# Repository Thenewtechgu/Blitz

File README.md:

# Blitz
Blitz is a MIMXRT1062DVJ6B based flight controller with dual Rp2350B for navigation and telemetry

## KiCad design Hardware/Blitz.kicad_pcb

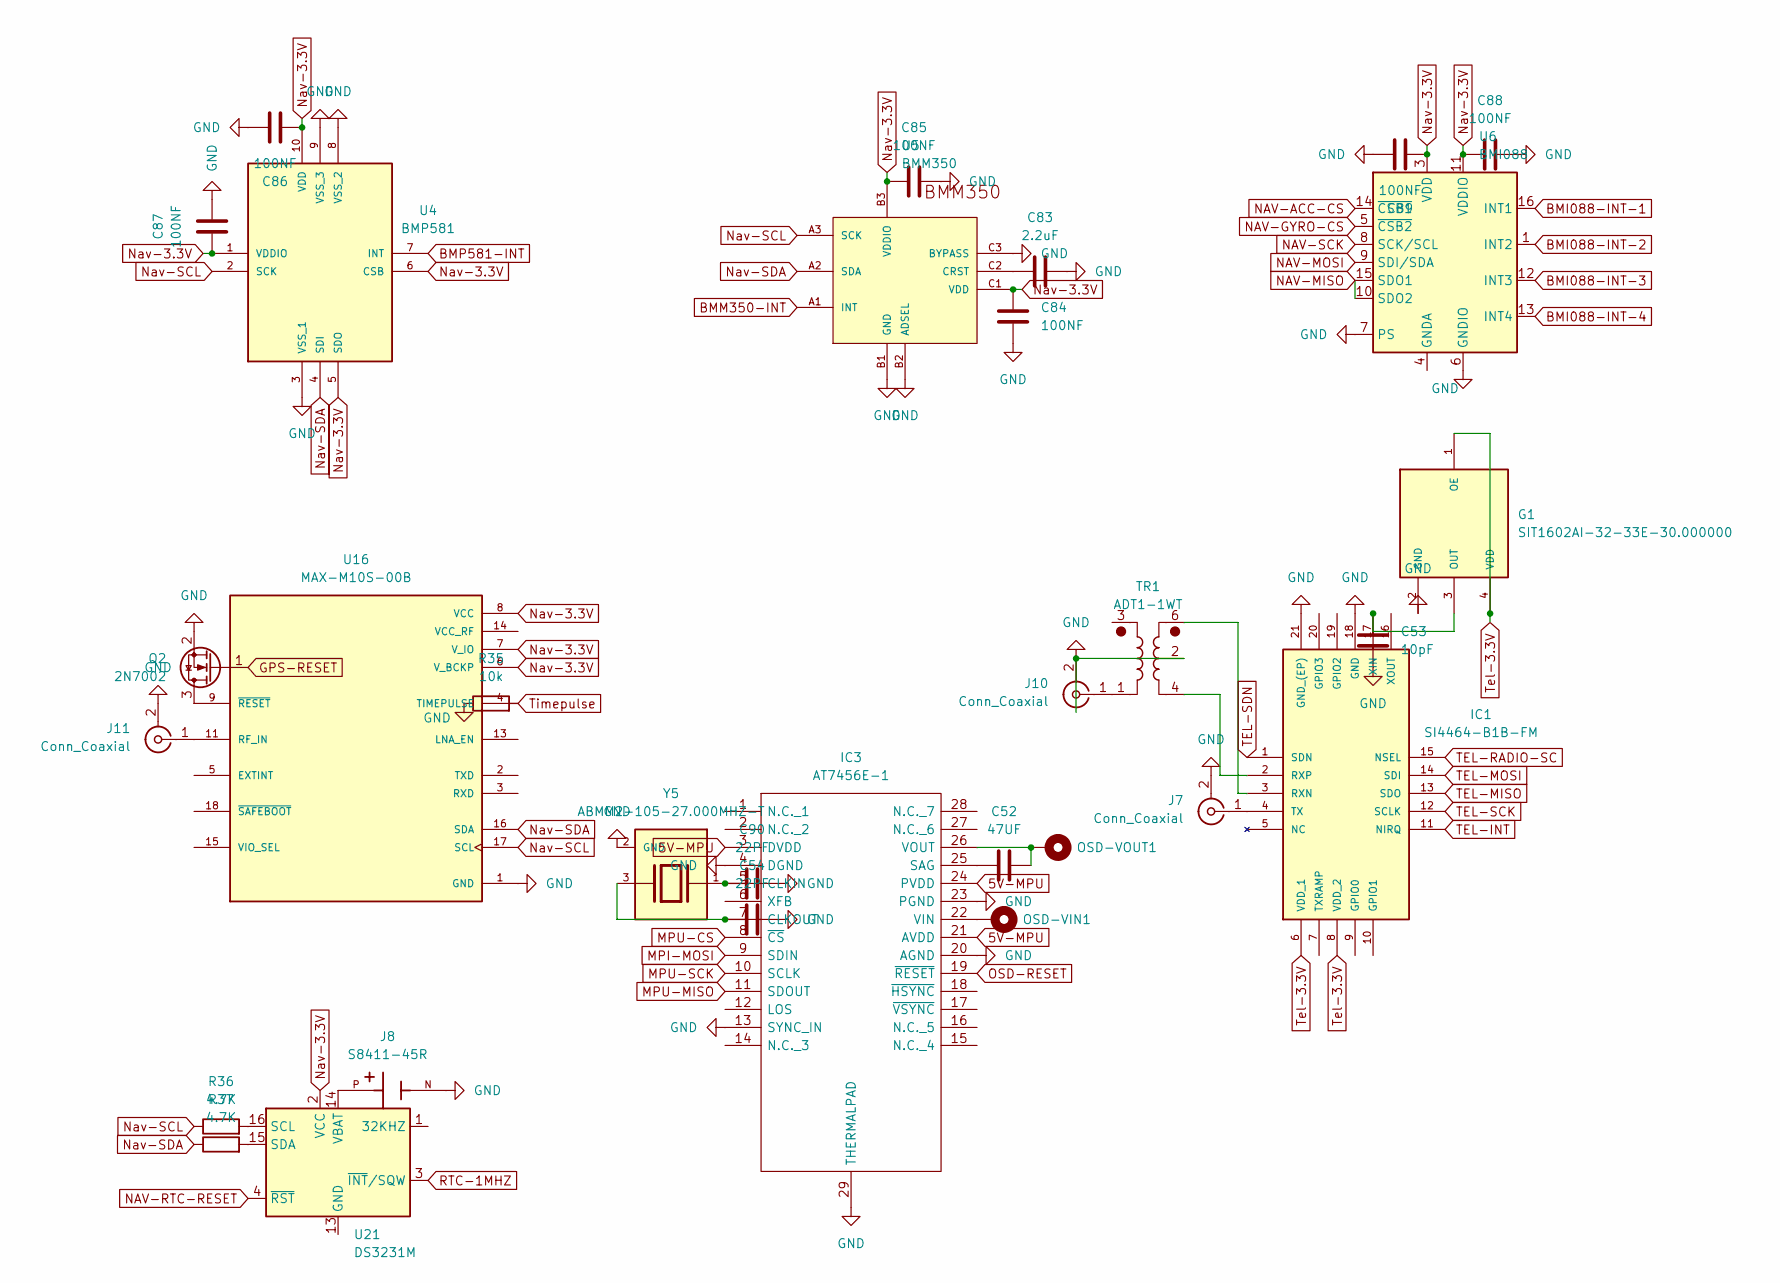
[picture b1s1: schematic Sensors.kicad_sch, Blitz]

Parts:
C52: 47UF; C_0402_1005Metric
C53: 10pF; C_0201_0603Metric
C54, C90: 22PF
C83: 2.2uF; C_0201_0603Metric
C84, C85, C86, C87, C88, C89: 100NF; C_0201_0603Metric
G1: SIT1602AI-32-33E-30.000000; OSC_SIT1602AI-32-33E-30.000000; PARTREV 1.2
IC1: SI4464-B1B-FM; QFN50P400X400X90-21N; MOUSER_PART_NUMBER 634-SI4464-B1X-FM
IC3: AT7456E-1; SOP65P640X120-29N; Manufacturer_Part_Number AT7456E
J7, J10, J11: Conn_Coaxial; SMA_Amphenol_901-143_Horizontal
J8: S8411-45R; HARWIN_S8411-45R; PARTREV 4
OSD-VIN1: Solderpad; TestPoint_Pad_1.5x1.5mm
OSD-VOUT1: Solderpad; TestPoint_Pad_1.5x1.5mm
Q2: 2N7002; SOT-23
R35: 10k; R_0201_0603Metric
R36, R37: 4.7K; R_0201_0603Metric
TR1: ADT1-1WT; Mini-Circuits_CD542_H2.84mm
U4: BMP581; Manufacturer_Part_Number BMP581
U5: BMM350; BGA9C40P3X3_128X128X50
U6: BMI088; Bosch_LGA-16_4.5x3mm_P0.5mm_LayoutBorder7x1y_ClockwisePinNu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
U16: MAX-M10S-00B; XCVR_MAX-M10S-00B; PARTREV C1
U21: DS3231M; SOIC-16W_7.5x10.3mm_P1.27mm
Y5: ABMM2-105-27.000MHZ-T; XTAL_ABMM2-105-27.000MHZ-T; PARTREV 01.18.13

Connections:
5V-MPU: IC3.3 (DVDD), IC3.21 (AVDD), IC3.24 (PVDD); also elsewhere on the board
BMI088-INT-1: U6.16 (INT1); also elsewhere on the board
BMI088-INT-2: U6.1 (INT2); also elsewhere on the board
BMI088-INT-3: U6.12 (INT3); also elsewhere on the board
BMI088-INT-4: U6.13 (INT4); also elsewhere on the board
BMM350-INT: U5.A1 (INT); also elsewhere on the board
BMP581-INT: U4.7 (INT); also elsewhere on the board
GPS-RESET: Q2.1 (G); also elsewhere on the board
MPI-MOSI: IC3.9 (SDIN); also elsewhere on the board
MPU-CS: IC3.8 (~CS); also elsewhere on the board
MPU-MISO: IC3.11 (SDOUT); also elsewhere on the board
MPU-SCK: IC3.10 (SCLK); also elsewhere on the board
NAV-ACC-CS: U6.14 (~CSB1); also elsewhere on the board
NAV-GYRO-CS: U6.5 (~CSB2); also elsewhere on the board
NAV-MISO: U6.10 (SDO2), U6.15 (SDO1); also elsewhere on the board
NAV-MOSI: U6.9 (SDI/SDA); also elsewhere on the board
NAV-RTC-RESET: U21.4 (~RST)
NAV-SCK: U6.8 (SCK/SCL); also elsewhere on the board
Nav-3.3V: C84.1, C85.1, C86.1, C87.1, C88.1, C89.1, U4.1 (VDDIO), U4.5 (SDO), U4.6 (CSB), U4.10 (VDD), U5.B3 (VDDIO), U5.C1 (VDD), U6.3 (VDD), U6.11 (VDDIO), U16.6 (V_BCKP), U16.7 (V_IO), U16.8 (VCC), U21.2 (VCC); also elsewhere on the board
Nav-SCL: R36.1, U4.2 (SCK), U5.A3 (SCK), U16.17 (SCL)
Nav-SDA: R37.1, U4.4 (SDI), U5.A2 (SDA), U16.16 (SDA)
unnamed: C53.1, G1.3 (OUT), IC1.17 (XIN)
unnamed: IC1.3 (RXN), TR1.6
unnamed: IC1.2 (RXP), TR1.4
unnamed: IC1.4 (TX), J7.1 (In)
unnamed: C90.1, IC3.5 (CLKIN), Y5.1
unnamed: C54.1, IC3.7 (CLKOUT), Y5.3
unnamed: C52.1, IC3.25 (SAG)
unnamed: IC3.22 (VIN), OSD-VIN1.1
unnamed: C52.2, IC3.26 (VOUT), OSD-VOUT1.1
unnamed: J10.1 (In), TR1.1
unnamed: J11.1 (In), U16.11 (RF_IN)
unnamed: Q2.3 (D), U16.9 (~RESET)
unnamed: C83.1, U5.C2 (CRST)
unnamed: U6.2 (GNDA), U6.4 (GNDA)
unnamed: U21.5 (GND), U21.6 (GND), U21.7 (GND), U21.8 (GND), U21.9 (GND), U21.10 (GND), U21.11 (GND), U21.12 (GND), U21.13 (GND)
unnamed: R36.2, U21.16 (SCL)
unnamed: R37.2, U21.15 (SDA)
unnamed: J8.P, U21.14 (VBAT)
OSD-RESET: IC3.19 (~RESET); also elsewhere on the board
RTC-1MHZ: U21.3 (~INT/SQW); also elsewhere on the board
TEL-INT: IC1.11 (NIRQ); also elsewhere on the board
TEL-MISO: IC1.13 (SDO); also elsewhere on the board
TEL-MOSI: IC1.14 (SDI); also elsewhere on the board
TEL-RADIO-SC: IC1.15 (NSEL); also elsewhere on the board
TEL-SCK: IC1.12 (SCLK); also elsewhere on the board
TEL-SDN: IC1.1 (SDN); also elsewhere on the board
Tel-3.3V: G1.1 (OE), G1.4 (VDD), IC1.6 (VDD_1), IC1.8 (VDD_2); also elsewhere on the board
Timepulse: R35.2, U16.4 (TIMEPULSE); also elsewhere on the board

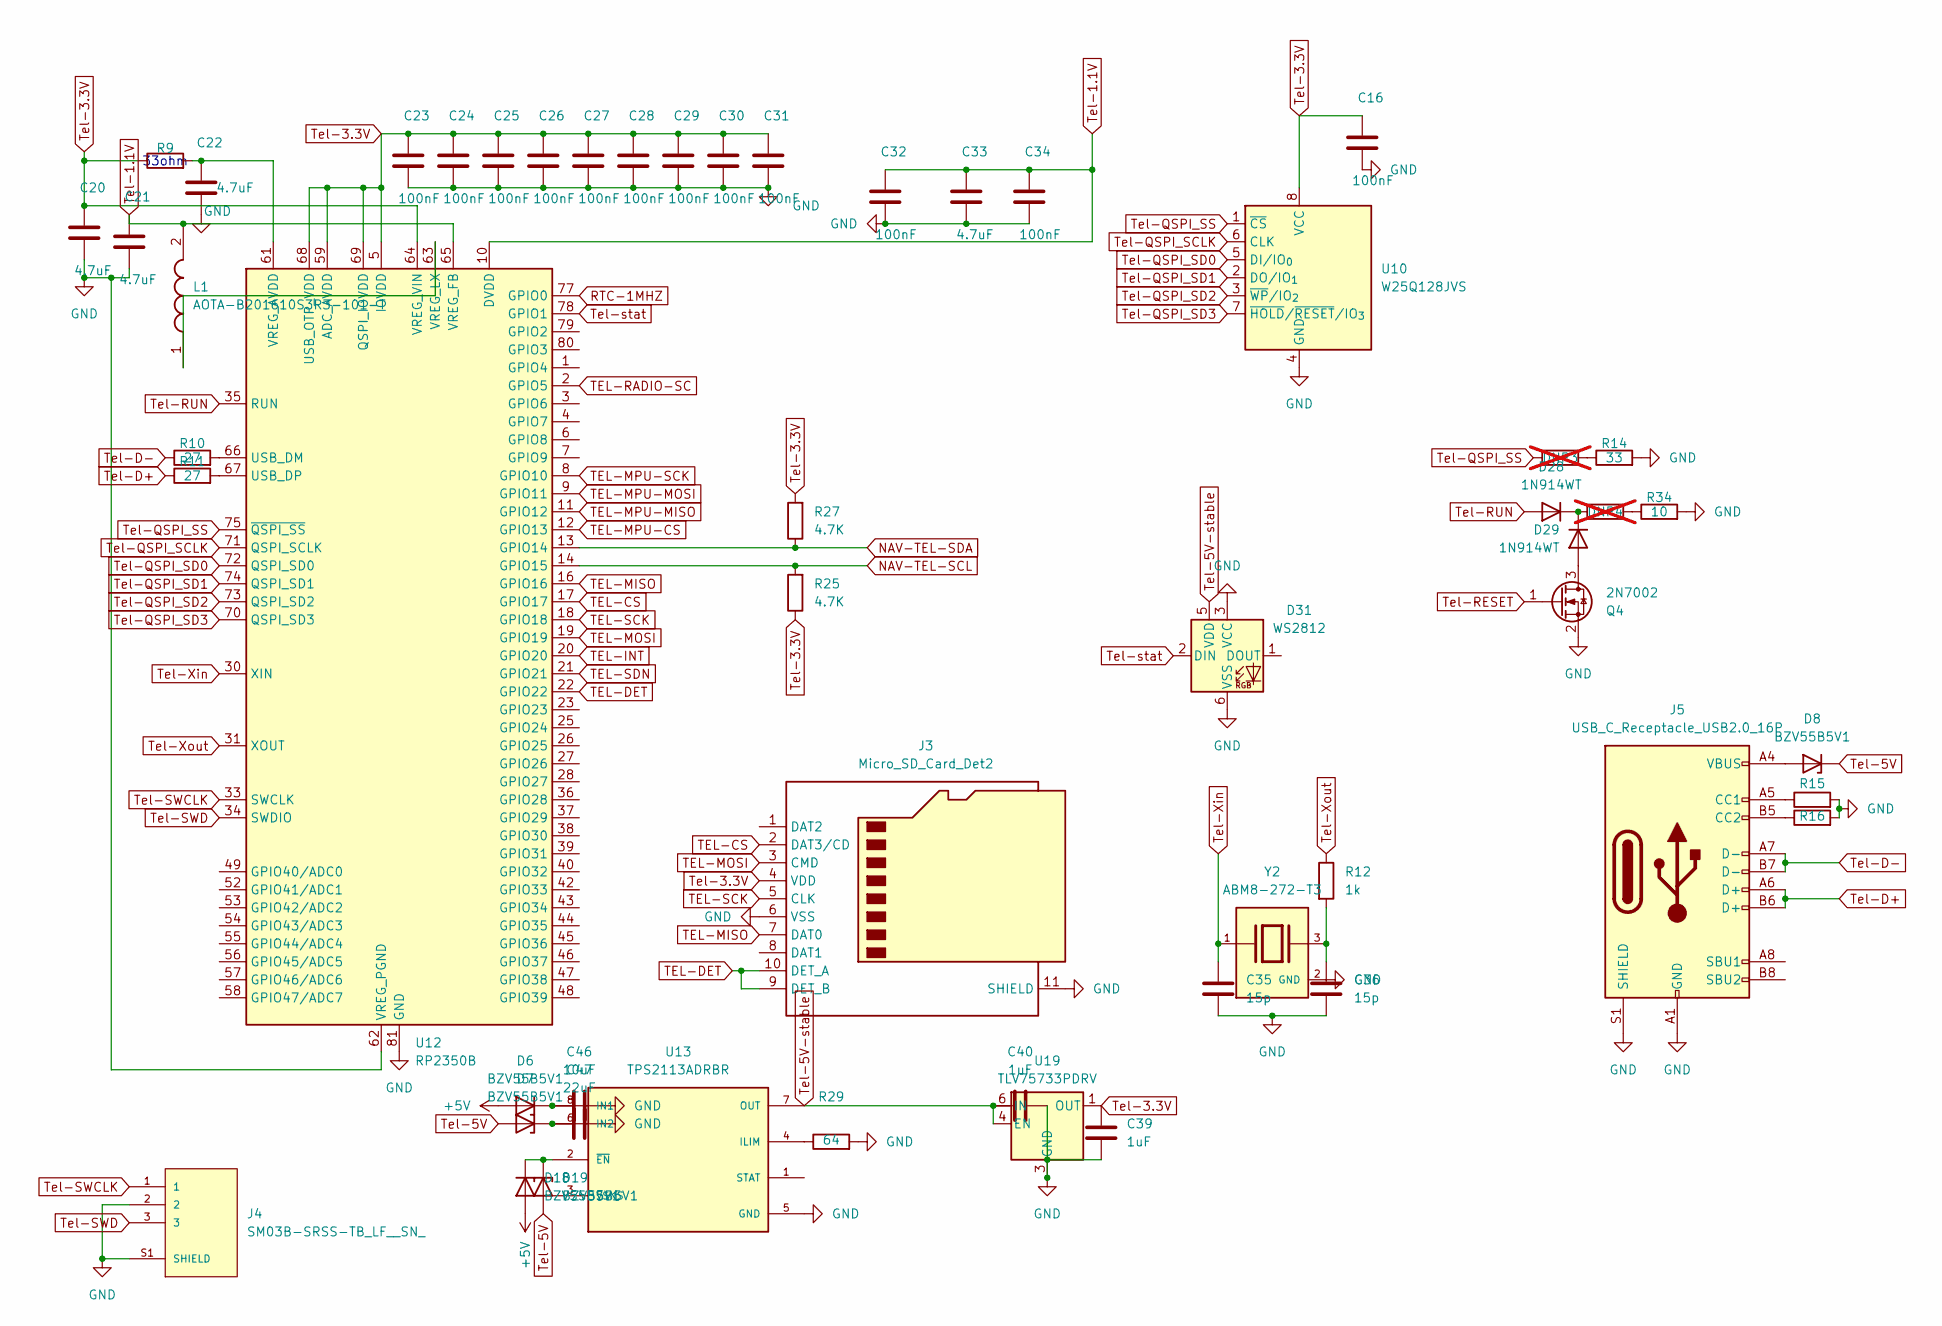
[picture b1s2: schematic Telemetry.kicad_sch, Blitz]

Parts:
C16, C23, C24, C25, C26, C27, C28, C29, C30, C31, C32, C34: 100nF; C_01005_0402Metric
C20, C21, C22, C33: 4.7uF; C_01005_0402Metric
C35, C36: 15p; C_0201_0603Metric
C39, C40: 1uF; C_0402_1005Metric
C46: 10uF; C_1206_3216Metric_Pad1.33x1.80mm_HandSolder
C47: 22uF; C_1206_3216Metric_Pad1.33x1.80mm_HandSolder
D6, D7, D8, D18, D19: BZV55B5V1; D_MiniMELF
D28, D29: 1N914WT; D_SOD-523
D31: WS2812; LED_WS2812_PLCC6_5.0x5.0mm_P1.6mm
DNP3, DNP4: R; R_2010_5025Metric_Pad1.40x2.65mm_HandSolder; not fitted
J3: Micro_SD_Card_Det2; microSD_HC_Molex_104031-0811
J4: SM03B-SRSS-TB_LF__SN_; JST_SM03B-SRSS-TB_LF__SN_
J5: USB_C_Receptacle_USB2.0_16P; USB_C_Receptacle_G-Switch_GT-USB-7010ASV
L1: AOTA-B201610S3R3-101-T; AOTAB201610S3R3101T; Manufacturer_Part_Number AOTA-B201610S3R3-101-T; Mouser Part Number 815-AB201610S3R3101T
Q4: 2N7002; SOT-23
R9: R; R_01005_0402Metric_Pad0.57x0.30mm_HandSolder
R10, R11: 27; R_0201_0603Metric_Pad0.64x0.40mm_HandSolder
R12: 1k; R_01005_0402Metric
R14: 33; R_0201_0603Metric_Pad0.64x0.40mm_HandSolder
R15, R16: R; R_01005_0402Metric
R25, R27: 4.7K; R_0201_0603Metric
R29: 64; R_0201_0603Metric
R34: 10; R_0201_0603Metric_Pad0.64x0.40mm_HandSolder
U10: W25Q128JVS; SOIC-8_5.3x5.3mm_P1.27mm
U12: RP2350B; QFN-80-1EP_10x10mm_P0.4mm_EP3.4x3.4mm
U13: TPS2113ADRBR; SON65P300X300X100-9N; PARTREV C
U19: TLV75733PDRV; WSON-6-1EP_2x2mm_P0.65mm_EP1x1.6mm
Y2: ABM8-272-T3; XTAL_ABM8-272-T3; PARTREV 07-29-20

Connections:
+5V: D6.2 (A), D18.2 (A); also elsewhere on the board
NAV-TEL-SCL: R25.2, U12.14 (GPIO15); also elsewhere on the board
NAV-TEL-SDA: R27.1, U12.13 (GPIO14); also elsewhere on the board
unnamed: C36.1, R12.2, Y2.3
unnamed: C46.1, D6.1 (K), U13.8 (IN1)
unnamed: C47.1, D7.1 (K), U13.6 (IN2)
unnamed: D8.2 (A), J5.A4 (VBUS), J5.A9 (VBUS), J5.B4 (VBUS), J5.B9 (VBUS)
unnamed: D18.1 (K), D19.1 (K), U13.2 (~EN)
unnamed: D28.1 (K), D29.1 (K), DNP4.1
unnamed: D29.2 (A), Q4.3 (D)
unnamed: DNP3.2, R14.1
unnamed: DNP4.2, R34.1
unnamed: J5.A5 (CC1), R15.1
unnamed: J5.B5 (CC2), R16.1
unnamed: R10.2, U12.66 (USB_DM)
unnamed: R11.2, U12.67 (USB_DP)
unnamed: C22.1, R9.2, U12.61 (VREG_AVDD)
unnamed: L1.1, U12.63 (VREG_LX)
unnamed: R29.1, U13.4 (ILIM)
RTC-1MHZ: U12.77 (GPIO0); also elsewhere on the board
TEL-CS: J3.2 (DAT3/CD), U12.17 (GPIO17)
TEL-DET: J3.9 (DET_B), J3.10 (DET_A), U12.22 (GPIO22)
TEL-INT: U12.20 (GPIO20); also elsewhere on the board
TEL-MISO: J3.7 (DAT0), U12.16 (GPIO16); also elsewhere on the board
TEL-MOSI: J3.3 (CMD), U12.19 (GPIO19); also elsewhere on the board
TEL-MPU-CS: U12.12 (GPIO13); also elsewhere on the board
TEL-MPU-MISO: U12.11 (GPIO12); also elsewhere on the board
TEL-MPU-MOSI: U12.9 (GPIO11); also elsewhere on the board
TEL-MPU-SCK: U12.8 (GPIO10); also elsewhere on the board
TEL-RADIO-SC: U12.2 (GPIO5); also elsewhere on the board
TEL-SCK: J3.5 (CLK), U12.18 (GPIO18); also elsewhere on the board
TEL-SDN: U12.21 (GPIO21); also elsewhere on the board
Tel-1.1V: C21.1, C32.1, C33.1, C34.1, L1.2, U12.10 (DVDD), U12.32 (DVDD), U12.51 (DVDD), U12.65 (VREG_FB)
Tel-3.3V: C16.1, C20.1, C23.1, C24.1, C25.1, C26.1, C27.1, C28.1, C29.1, C30.1, C31.1, C39.1, J3.4 (VDD), R9.1, R25.1, R27.2, U10.8 (VCC), U12.5 (IOVDD), U12.15 (IOVDD), U12.24 (IOVDD), U12.29 (IOVDD), U12.41 (IOVDD), U12.50 (IOVDD), U12.59 (ADC_AVDD), U12.60 (IOVDD), U12.64 (VREG_VIN), U12.68 (USB_OTP_VDD), U12.69 (QSPI_IOVDD), U12.76 (IOVDD), U19.1 (OUT); also elsewhere on the board
Tel-5V: D7.2 (A), D8.1 (K), D19.2 (A)
Tel-5V-stable: C40.1, D31.5 (VDD), U13.7 (OUT), U19.4 (EN), U19.6 (IN)
Tel-D+: J5.A6 (D+), J5.B6 (D+), R11.1
Tel-D-: J5.A7 (D-), J5.B7 (D-), R10.1
Tel-QSPI_SCLK: U10.6 (CLK), U12.71 (QSPI_SCLK)
Tel-QSPI_SD0: U10.5 (DI/IO_{0}), U12.72 (QSPI_SD0)
Tel-QSPI_SD1: U10.2 (DO/IO_{1}), U12.74 (QSPI_SD1)
Tel-QSPI_SD2: U10.3 (~WP/IO_{2}), U12.73 (QSPI_SD2)
Tel-QSPI_SD3: U10.7 (~HOLD/~RESET/IO_{3}), U12.70 (QSPI_SD3)
Tel-QSPI_SS: DNP3.1, U10.1 (~CS), U12.75 (~QSPI_SS)
Tel-RESET: Q4.1 (G)
Tel-RUN: D28.2 (A), U12.35 (RUN)
Tel-SWCLK: J4.1, U12.33 (SWCLK)
Tel-SWD: J4.3, U12.34 (SWDIO)
Tel-Xin: C35.1, U12.30 (XIN), Y2.1
Tel-Xout: R12.1, U12.31 (XOUT)
Tel-stat: D31.2 (DIN), U12.78 (GPIO1)

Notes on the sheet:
33ohm

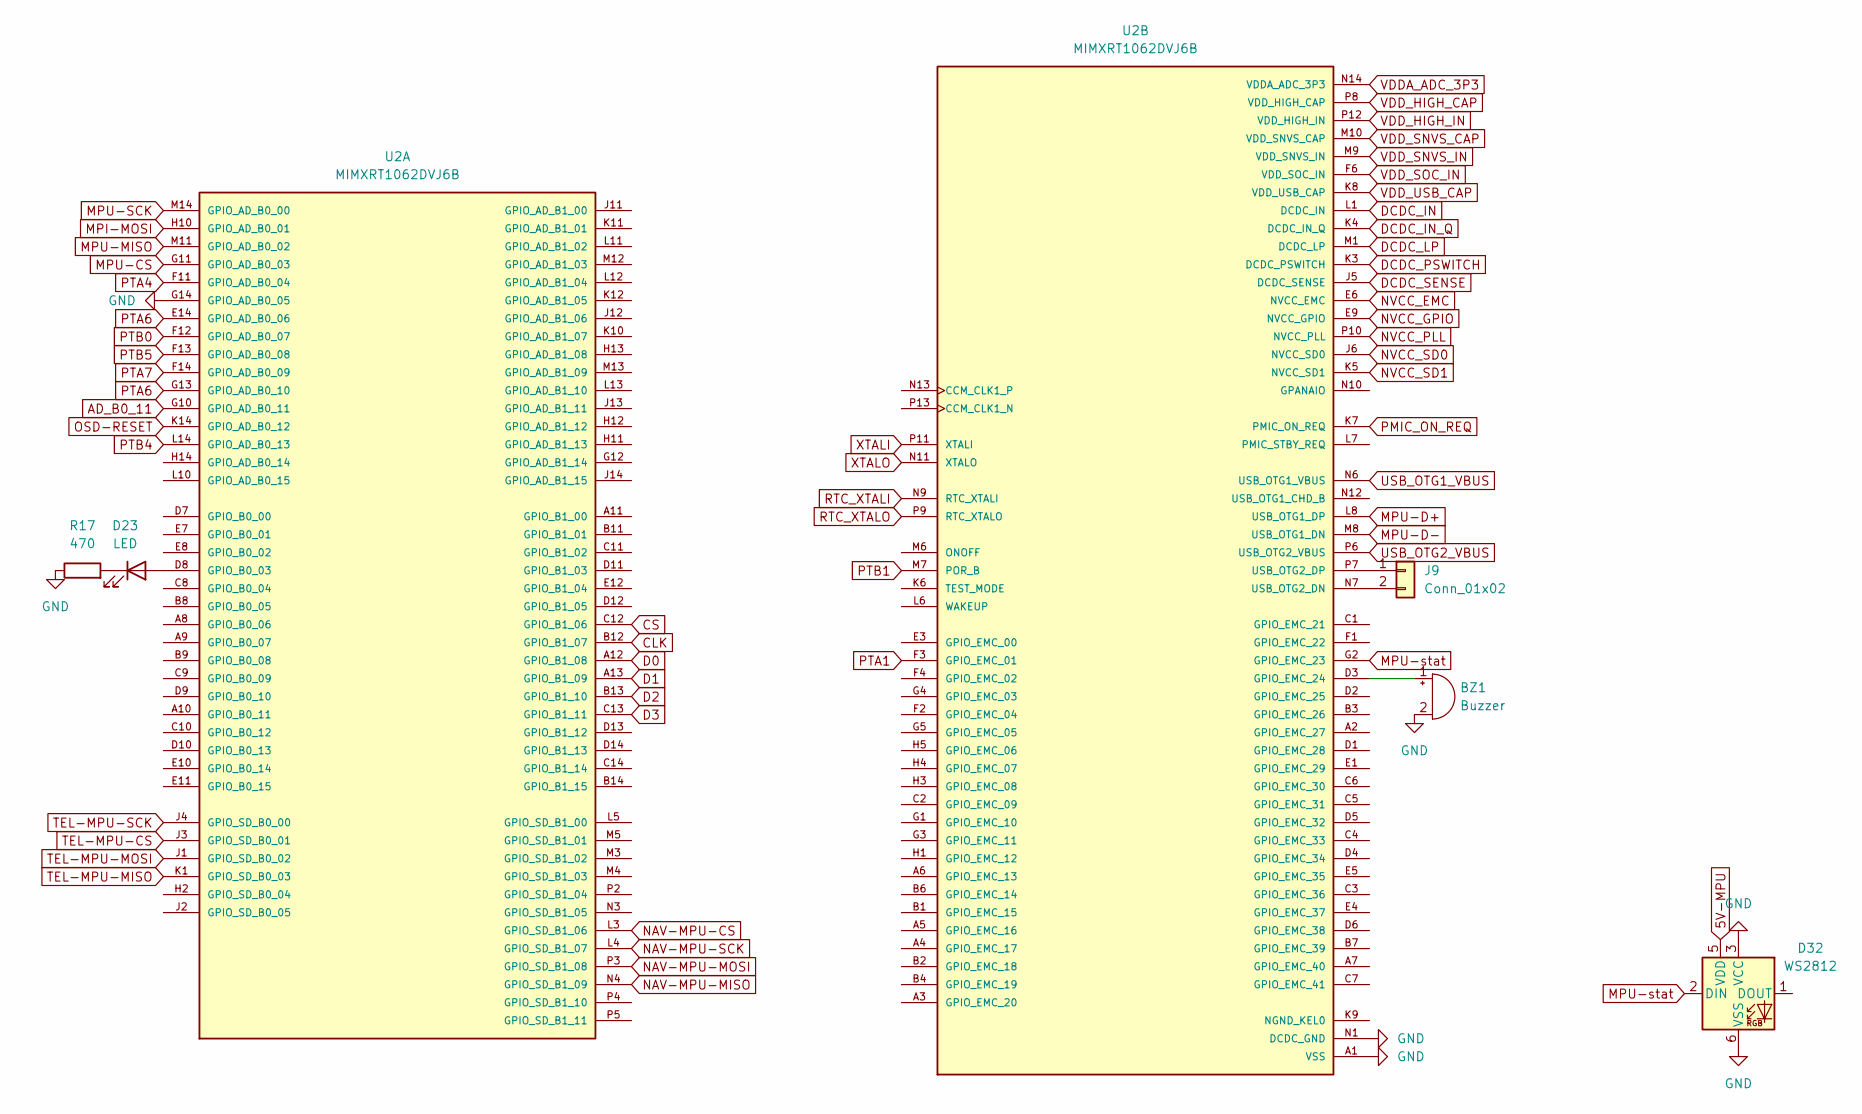
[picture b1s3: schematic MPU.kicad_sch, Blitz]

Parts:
BZ1: Buzzer; MLT-8530_JHE_1
D23: LED; LED_1206_3216Metric_Pad1.42x1.75mm_HandSolder
D32: WS2812; LED_WS2812_PLCC6_5.0x5.0mm_P1.6mm
J9: Conn_01x02; PinSocket_1x02_P1.00mm_Vertical
R17: 470; R_0201_0603Metric_Pad0.64x0.40mm_HandSolder
U2: MIMXRT1062DVJ6B; BGA196C80P14X14_1200X1200X152N; PARTREV 3

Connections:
5V-MPU: D32.5 (VDD); also elsewhere on the board
AD_B0_11: U2.G10 (GPIO_AD_B0_11), U2.K3 (DCDC_PSWITCH); also elsewhere on the board
CLK: U2.B12 (GPIO_B1_07); also elsewhere on the board
CS: U2.C12 (GPIO_B1_06); also elsewhere on the board
D0: U2.A12 (GPIO_B1_08); also elsewhere on the board
D1: U2.A13 (GPIO_B1_09); also elsewhere on the board
D2: U2.B13 (GPIO_B1_10); also elsewhere on the board
D3: U2.C13 (GPIO_B1_11); also elsewhere on the board
DCDC_IN: U2.L1 (DCDC_IN), U2.L2 (DCDC_IN); also elsewhere on the board
DCDC_IN_Q: U2.E6 (NVCC_EMC), U2.E9 (NVCC_GPIO), U2.F5 (NVCC_EMC), U2.F6 (VDD_SOC_IN), U2.F7 (VDD_SOC_IN), U2.F8 (VDD_SOC_IN), U2.F9 (VDD_SOC_IN), U2.F10 (NVCC_GPIO), U2.G6 (VDD_SOC_IN), U2.G9 (VDD_SOC_IN), U2.H6 (VDD_SOC_IN), U2.H9 (VDD_SOC_IN), U2.J5 (DCDC_SENSE), U2.J6 (NVCC_SD0), U2.J9 (VDD_SOC_IN), U2.J10 (NVCC_GPIO), U2.K4 (DCDC_IN_Q), U2.K5 (NVCC_SD1), U2.N14 (VDDA_ADC_3P3), U2.P12 (VDD_HIGH_IN); also elsewhere on the board
DCDC_LP: U2.M1 (DCDC_LP), U2.M2 (DCDC_LP); also elsewhere on the board
MPI-MOSI: U2.H10 (GPIO_AD_B0_01); also elsewhere on the board
MPU-CS: U2.G11 (GPIO_AD_B0_03); also elsewhere on the board
MPU-D+: U2.L8 (USB_OTG1_DP); also elsewhere on the board
MPU-D-: U2.M8 (USB_OTG1_DN); also elsewhere on the board
MPU-MISO: U2.M11 (GPIO_AD_B0_02); also elsewhere on the board
MPU-SCK: U2.M14 (GPIO_AD_B0_00); also elsewhere on the board
MPU-stat: D32.2 (DIN), U2.G2 (GPIO_EMC_23)
NAV-MPU-CS: U2.L3 (GPIO_SD_B1_06); also elsewhere on the board
NAV-MPU-MISO: U2.N4 (GPIO_SD_B1_09); also elsewhere on the board
NAV-MPU-MOSI: U2.P3 (GPIO_SD_B1_08); also elsewhere on the board
NAV-MPU-SCK: U2.L4 (GPIO_SD_B1_07); also elsewhere on the board
NVCC_PLL: U2.P10 (NVCC_PLL); also elsewhere on the board
unnamed: BZ1.1 (+), U2.D3 (GPIO_EMC_24)
unnamed: D23.2 (A), U2.D8 (GPIO_B0_03)
unnamed: D23.1 (K), R17.2
unnamed: J9.1, U2.P7 (USB_OTG2_DP)
unnamed: J9.2, U2.N7 (USB_OTG2_DN)
OSD-RESET: U2.K14 (GPIO_AD_B0_12); also elsewhere on the board
PMIC_ON_REQ: U2.K7 (PMIC_ON_REQ); also elsewhere on the board
PTA1: U2.F3 (GPIO_EMC_01); also elsewhere on the board
PTA4: U2.F11 (GPIO_AD_B0_04); also elsewhere on the board
PTA6: U2.E14 (GPIO_AD_B0_06), U2.G13 (GPIO_AD_B0_10); also elsewhere on the board
PTA7: U2.F14 (GPIO_AD_B0_09); also elsewhere on the board
PTB0: U2.F12 (GPIO_AD_B0_07); also elsewhere on the board
PTB1: U2.M7 (POR_B); also elsewhere on the board
PTB4: U2.L14 (GPIO_AD_B0_13); also elsewhere on the board
PTB5: U2.F13 (GPIO_AD_B0_08); also elsewhere on the board
RTC_XTALI: U2.N9 (RTC_XTALI); also elsewhere on the board
RTC_XTALO: U2.P9 (RTC_XTALO); also elsewhere on the board
TEL-MPU-CS: U2.J3 (GPIO_SD_B0_01); also elsewhere on the board
TEL-MPU-MISO: U2.K1 (GPIO_SD_B0_03); also elsewhere on the board
TEL-MPU-MOSI: U2.J1 (GPIO_SD_B0_02); also elsewhere on the board
TEL-MPU-SCK: U2.J4 (GPIO_SD_B0_00); also elsewhere on the board
USB_OTG1_VBUS: U2.N6 (USB_OTG1_VBUS), U2.P6 (USB_OTG2_VBUS); also elsewhere on the board
VDD_HIGH_CAP: U2.P8 (VDD_HIGH_CAP); also elsewhere on the board
VDD_SNVS_CAP: U2.M10 (VDD_SNVS_CAP); also elsewhere on the board
VDD_SNVS_IN: U2.M9 (VDD_SNVS_IN); also elsewhere on the board
VDD_USB_CAP: U2.K8 (VDD_USB_CAP); also elsewhere on the board
XTALI: U2.P11 (XTALI); also elsewhere on the board
XTALO: U2.N11 (XTALO); also elsewhere on the board

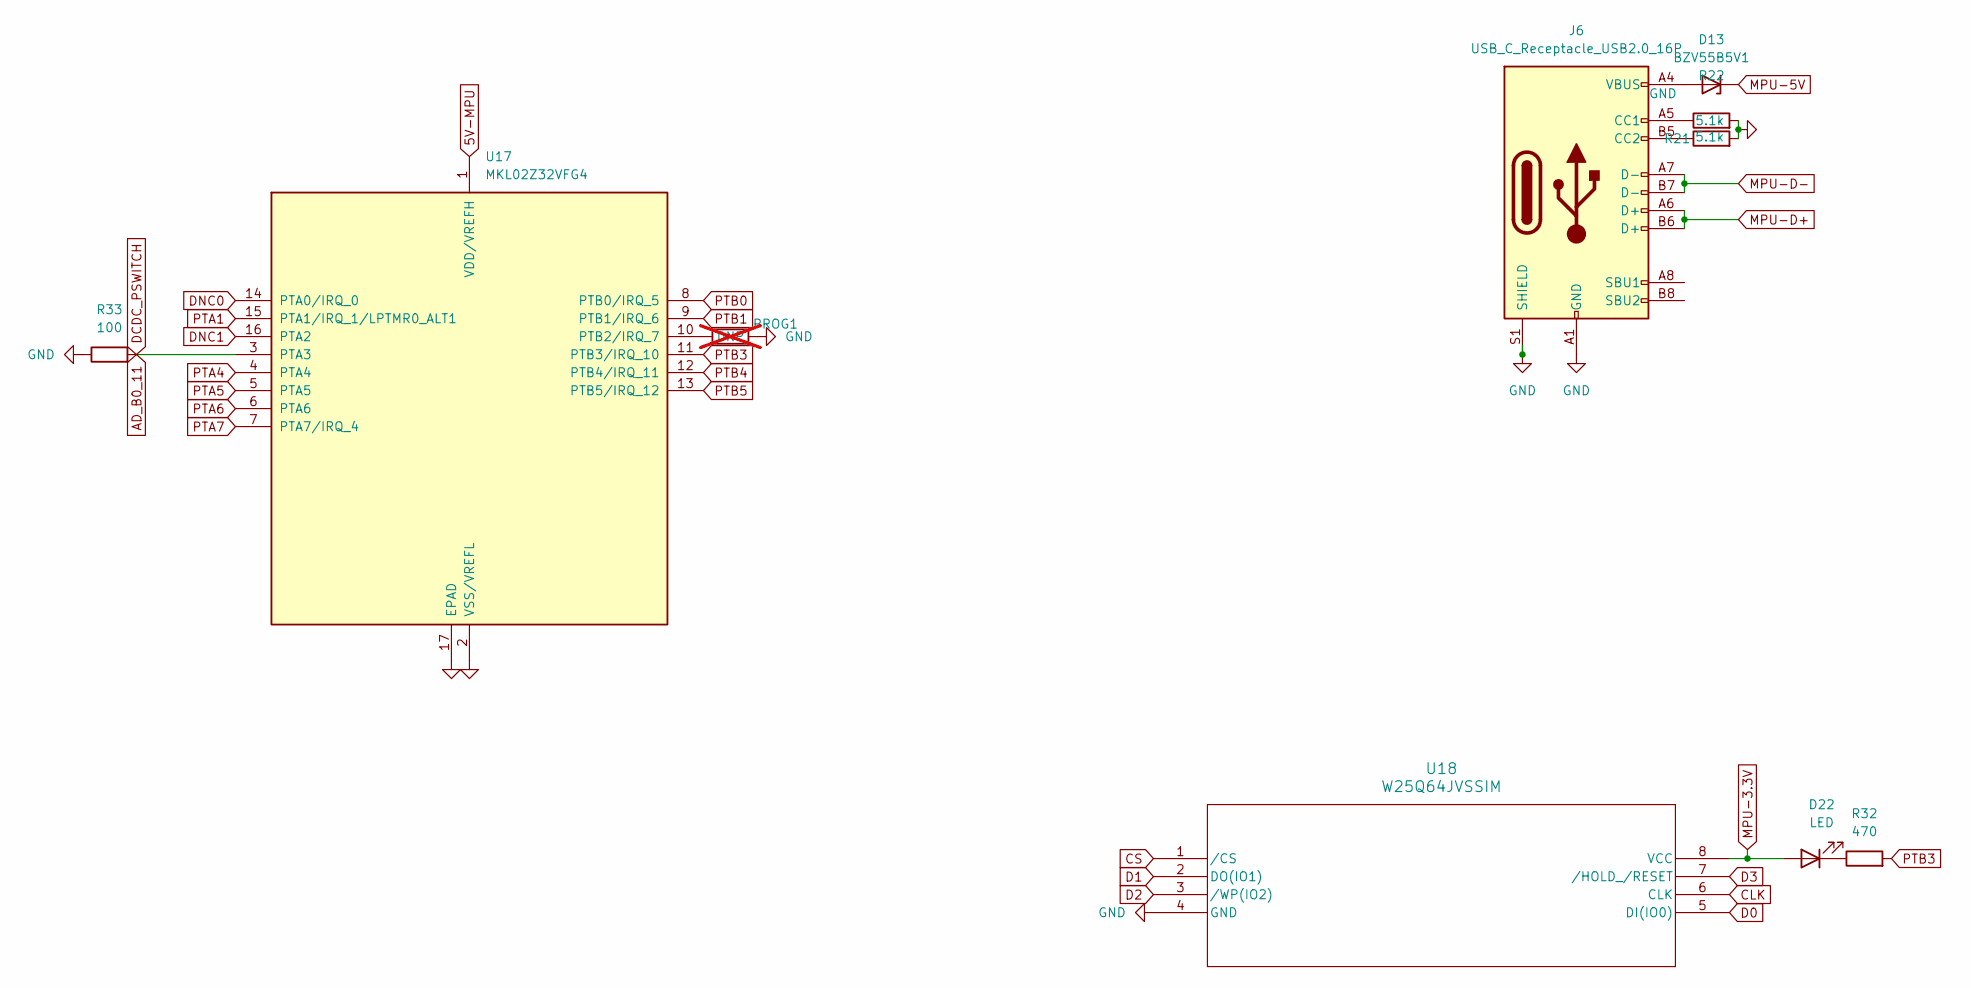
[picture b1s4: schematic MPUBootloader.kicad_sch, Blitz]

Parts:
D13: BZV55B5V1; D_MiniMELF
D22: LED; LED_1206_3216Metric
J6: USB_C_Receptacle_USB2.0_16P; USB_C_Receptacle_G-Switch_GT-USB-7010ASV
PROG1: DNP; R_2010_5025Metric_Pad1.40x2.65mm_HandSolder; not fitted
R21, R22: 5.1k; R_0201_0603Metric
R32: 470; R_0201_0603Metric
R33: 100; R_0201_0603Metric
U17: MKL02Z32VFG4; QFN-16-1EP_3x3mm_P0.5mm_EP1.9x1.9mm
U18: W25Q64JVSSIM; SOIC_208MIL_WIN

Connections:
5V-MPU: U17.1 (VDD/VREFH); also elsewhere on the board
AD_B0_11: R33.2, U17.3 (PTA3); also elsewhere on the board
CLK: U18.6 (CLK); also elsewhere on the board
CS: U18.1 (/CS); also elsewhere on the board
D0: U18.5 (DI(IO0)); also elsewhere on the board
D1: U18.2 (DO(IO1)); also elsewhere on the board
D2: U18.3 (/WP(IO2)); also elsewhere on the board
D3: U18.7 (/HOLD_/RESET); also elsewhere on the board
DCDC_IN_Q: D22.2 (A), U18.8 (VCC); also elsewhere on the board
DNC0: U17.14 (PTA0/IRQ_0)
DNC1: U17.16 (PTA2)
MPU-5V: D13.1 (K); also elsewhere on the board
MPU-D+: J6.A6 (D+), J6.B6 (D+); also elsewhere on the board
MPU-D-: J6.A7 (D-), J6.B7 (D-); also elsewhere on the board
unnamed: D13.2 (A), J6.A4 (VBUS), J6.A9 (VBUS), J6.B4 (VBUS), J6.B9 (VBUS)
unnamed: D22.1 (K), R32.1
unnamed: J6.A5 (CC1), R22.1
unnamed: J6.B5 (CC2), R21.1
unnamed: PROG1.1, U17.10 (PTB2/IRQ_7)
PTA1: U17.15 (PTA1/IRQ_1/LPTMR0_ALT1); also elsewhere on the board
PTA4: U17.4 (PTA4); also elsewhere on the board
PTA5: U17.5 (PTA5)
PTA6: U17.6 (PTA6); also elsewhere on the board
PTA7: U17.7 (PTA7/IRQ_4); also elsewhere on the board
PTB0: U17.8 (PTB0/IRQ_5); also elsewhere on the board
PTB1: U17.9 (PTB1/IRQ_6); also elsewhere on the board
PTB3: R32.2, U17.11 (PTB3/IRQ_10)
PTB4: U17.12 (PTB4/IRQ_11); also elsewhere on the board
PTB5: U17.13 (PTB5/IRQ_12); also elsewhere on the board

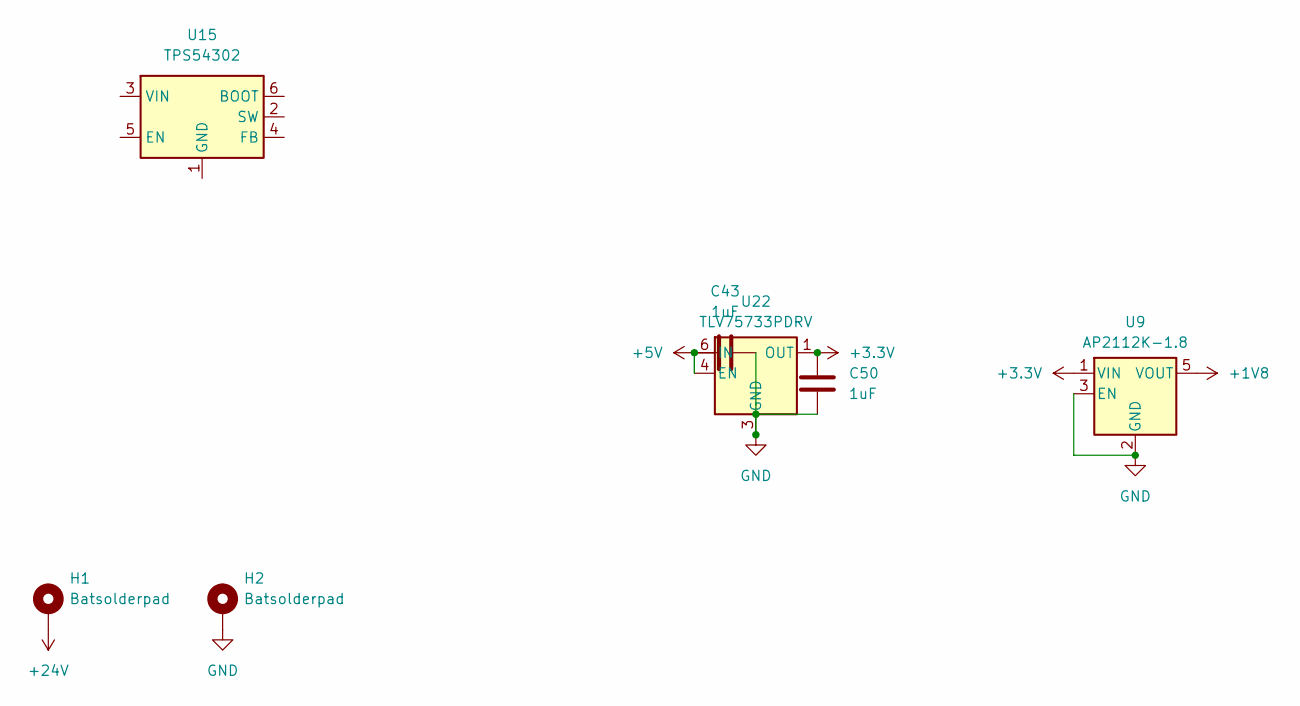
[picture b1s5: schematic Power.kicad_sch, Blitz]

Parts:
C43, C50: 1uF; C_1206_3216Metric_Pad1.33x1.80mm_HandSolder
H1, H2: Batsolderpad; TestPoint_Pad_4.0x4.0mm
U9: AP2112K-1.8; SOT-23-5
U15: TPS54302; SOT-23-6
U22: TLV75733PDRV; WSON-6-1EP_2x2mm_P0.65mm_EP1x1.6mm

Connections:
+1V8: U9.5 (VOUT)
+3.3V: C50.2, U9.1 (VIN), U22.1 (OUT)
+5V: C43.1, U22.4 (EN), U22.6 (IN); also elsewhere on the board
+24V: H1.1
